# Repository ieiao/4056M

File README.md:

# 4056M

Simple power module designed using TP4057 and CW2015.

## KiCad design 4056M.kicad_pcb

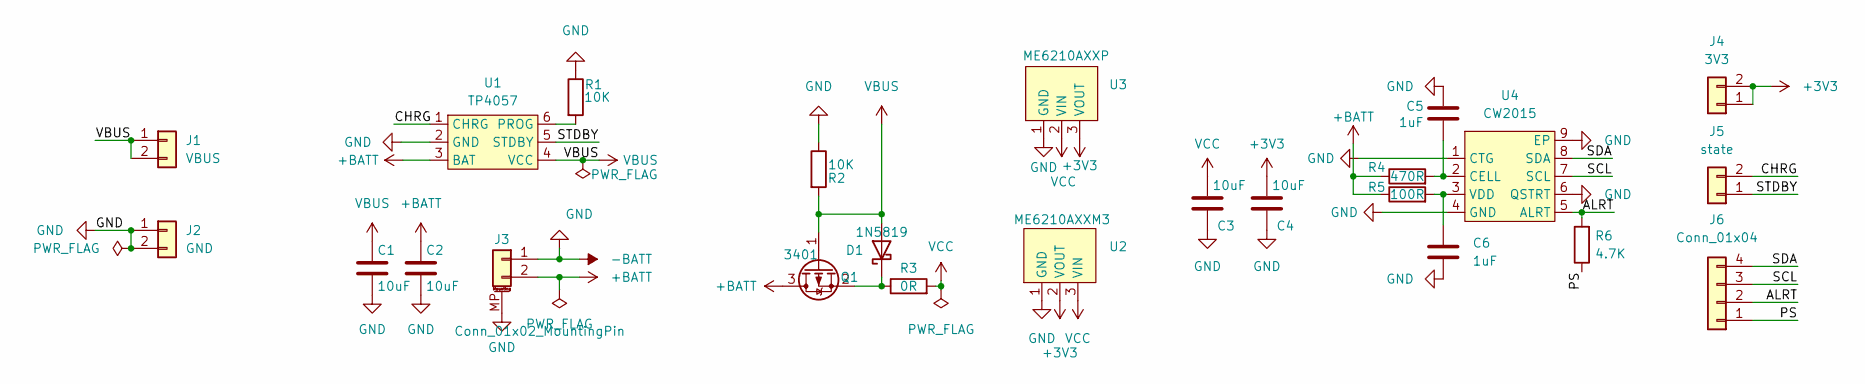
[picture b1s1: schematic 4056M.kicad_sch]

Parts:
C1, C3, C4: 10uF; C_0805_2012Metric
C2: 10uF; C_0603_1608Metric
C5, C6: 1uF; C_0603_1608Metric
D1: 1N5819; D_SOD-323
J1: VBUS; PinHeader_1x02_P1.27mm_Vertical
J2: GND; PinHeader_1x02_P1.27mm_Vertical
J3: Conn_01x02_MountingPin; JST_SH_SM02B-SRSS-TB_1x02-1MP_P1.00mm_Horizontal
J4: 3V3; PinHeader_1x02_P1.27mm_Vertical
J5: state; PinHeader_1x02_P1.27mm_Vertical
J6: Conn_01x04; PinHeader_1x04_P1.27mm_Vertical
Q1: 3401; SOT-23
R1: 10K; R_0603_1608Metric
R2: 10K; R_0402_1005Metric
R3: 0R; SolderJumper-2_P1.3mm_Bridged_RoundedPad1.0x1.5mm
R4: 470R; R_0603_1608Metric
R5: 100R; R_0603_1608Metric
R6: 4.7K; R_0603_1608Metric
U1: TP4057; SOT-23-6
U2: ME6210AXXM3; SOT-23-3
U3: ME6210AXXP; SOT-89-3
U4: CW2015; TDFN-8-1EP_3x2mm_P0.5mm_EP1.4x1.4mm

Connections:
+3V3: C4.2, J4.1, J4.2, U2.2 (VOUT), U3.3 (VOUT)
+BATT: C2.2, J3.2, Q1.3 (D), R4.1, R5.1, U1.3 (BAT)
-BATT: C1.1, C2.1, C3.1, C4.1, C5.1, C6.2, J2.1, J2.2, J3.1, J3.MP (MountPin), R1.1, R2.1, U1.2 (GND), U2.1 (GND), U3.1 (GND), U4.1 (CTG), U4.4 (GND), U4.6 (QSTRT), U4.9 (EP)
/ALRT: J6.2, R6.2, U4.5 (ALRT)
/CHRG: J5.2, U1.1 (CHRG)
/PS: J6.1, R6.1
/SCL: J6.3, U4.7 (SCL)
/SDA: J6.4, U4.8 (SDA)
/STDBY: J5.1, U1.5 (STDBY)
unnamed: C5.2, R4.2, U4.2 (CELL)
unnamed: C6.1, R5.2, U4.3 (VDD)
unnamed: D1.1 (K), Q1.2 (S), R3.1
unnamed: R1.2, U1.6 (PROG)
VBUS: C1.2, D1.2 (A), J1.1, J1.2, Q1.1 (G), R2.2, U1.4 (VCC)
VCC: C3.2, R3.2, U2.3 (VIN), U3.2 (VIN)

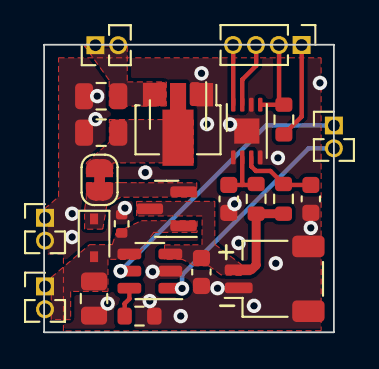
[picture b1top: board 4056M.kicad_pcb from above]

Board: 2 copper layers, 16.1 x 16.0 mm, 24 parts (0 on the bottom side), 15 nets.

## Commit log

2024-01-07 Init repository
2024-01-07 首次提交
2024-02-22 电池座PIN1应该为GND
2024-12-01 New version
2024-12-19 Add readme
